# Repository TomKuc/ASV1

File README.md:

# Ankle Sensor V1 — A1 warunki produkcyjne A01–A04

**CONDITIONAL READY dla3–5 prototypów JLCPCB.** Można rozpocząć wycenę/import i przegląd JLCPCB. Zwolnienie wykonania wymaga zamknięcia warunków A01–A04 z [raportu gotowości](docs/production_readiness_A1.md). Nie złożono zamówienia i nie wykonano testów sprzętowych. Nie ma jeszcze uruchomionego firmware.

Jedyna aktualna wersja: [manifest A1](reports/current_A1_manifest.json). PCB SHA256: `1d3bb700a2b686ef68589bf3295488d2144a1d51a857cec7651e45be175a6134`. Aktualna paczka: **Ankle_Sensor_V1_A1_PRODUCTION_REVIEW.zip**. Dawne ZIP A0/A1/AUDIT/FINAL i raporty bazowe są historią.

## Co otwierać

- [Projekt KiCad](hardware/Ankle_Sensor_V1.kicad_pro), [schemat](hardware/Ankle_Sensor_V1.kicad_sch), [poprowadzone PCB](hardware/Ankle_Sensor_V1.kicad_pcb). Obok musi pozostać [plik reguł](hardware/Ankle_Sensor_V1.kicad_dru); zawiera uzasadnioną regułę tylko dla pary USB.
- [PDF schematu](reports/Ankle_Sensor_V1_A1_schematic.pdf), [STEP do przeglądu](reports/Ankle_Sensor_V1_A1_mechanical_review.step), [render KiCad](reports/Ankle_Sensor_V1_A1_3d_review.png), [przewodnik dla początkujących](reports/guide/ankle_sensor_przewodnik.html).
- [BOM](manufacturing/review/assembly/BOM_REVIEW_NOT_RELEASED.csv), [CPL/Pick and Place](manufacturing/review/assembly/CPL_REVIEW_ROTATIONS_UNCONFIRMED.csv), [Gerber/Drill](manufacturing/review/Ankle_Sensor_V1_A1_GERBERS_DRILL_REVIEW.zip), [manifest eksportu](manufacturing/review/export_manifest.json).
- [Warunki zamówienia A/B/C](docs/release_checklist.md), [wybrany profil JLCPCB](hardware/manufacturing_profile_A1.json), [tabela stanów ładowania](docs/charge_startup_final_A1.md), [USB i obliczenia](docs/production_usb_A1.md), [PCBA i DFM](docs/production_pcba_dfm_A1.md).

## Stan projektu

69 footprintów,59 części montowanych na TOP,4 warstwy, obrys30×51.6mm, nominalnie1.0mm. Pamięć **W25Q01JVZEIQ128MiB** pozostaje; nie zmieniono architektury. INT1=P0.11, INT2=P0.12. Zachowano centra wszystkich ścieżek, via i części. W tym etapie zmieniono tylko C9 na 10 µF / CL10A106KP8NNNC / C19702 w tym samym 0603. Pełna geometria PCB jest identyczna z poprzednim etapem; USB pozostaje 0.17/0.13 mm.

Wybrany profil do potwierdzenia zamówienia to **JLC7628 4L/1.0mm, outer1oz/inner0.5oz, zielona maska/ENIG**. Model2D trunku daje około94Ω względem In1 i87Ω przy idealnym warunkowym odniesieniu pobliskiej3V0. Nie jest to kwalifikacja całego toru ani fizyczny test USB. Ogólny plik Gerber Job KiCad jest oddzielnym plikiem referencyjnym, wyłączonym z ZIP do uploadu.

Natywne KiCad10.0.7: **ERC0 błędów/2 uzasadnione ostrzeżenia IMU; DRC0 naruszeń,0opens,0rozbieżności schemat–PCB, brak ignorowanych klas**. [Wyniki i hashe wejść](reports/validation_status.json). Sprawdzono współrzędne59 CPL,164vias,4sloty PTH i2NPTH względem PCB. Nie zatwierdzono jeszcze podglądu rotacji/MPN/panelu w JLCPCB.

R24 jest pull-up: HIGH/HiZ blokuje ładowanie; LOW zwalnia je tylko za zgodą sprzętowego okna. Hang LOW i System OFF wymagają jawnej obsługi firmware. **Bez działającego firmware bateria nie ładuje się**, ale USB może zasilać SYS i umożliwić programowanie przez SWD. Pakiet/wiązka/NTC są oddzielnym zespołem i wymagają kwalifikacji przed prawdziwym ładowaniem.

A01–A04: **EXTERNAL CONFIRMATION**. C11/Ceff i dokładne landy U3/J1/Y1 do akceptacji; aktualny stack, procurement/rotacje oraz CAM/DFM do JLC. [Gotowe pytania do producentów](docs/JLCPCB_A1_confirmation_request.md), [59 części i 3 pozycje zewnętrzne](reports/production_component_status_A1.csv). Testy Flash/IMU/BLE/USB/termiki wykonuje się po otrzymaniu prototypów. Zachowano [20 prób Flash, wszystkie NOT_RUN](docs/flash_firmware_test_plan_A1.md).

STEP jest niekompletny: brak USB-C, ogólny Raytac, gabaryt Flash i ograniczenie wysokości IMU. Bateria/obudowa nie są w modelu. [Ograniczenia mechaniczne](docs/mechanical_model_review.md).

## Historia i GitHub

`b5487d09…` to A1 sprzed audytu; `38545441…` po audycie; `cdcbd234…` poprzednia korekta USB; `1d3bb700…` obecna korekta nominału C9. [Pochodzenie i zachowane paczki](reports/production_provenance_A1.json).

Bazowy lokalny commit: b17f145. Nie potwierdzono ce616878 ani aktualnej rewizji na GitHubie; nie wykonano push. Nowy commit i bundle opisuje `reports/production_commit_delivery_A1.json`, dostarczany po utworzeniu commita. [Import i weryfikacja serwera](docs/github_delivery_production_A1.md).

Natywne pliki `hardware/` są źródłem projektu. `build_pcb.py --replace` usuwa routing, a `build_design.py` nadpisuje schematy — nie uruchamiać ich na tej A1 bez zabezpieczonej kopii. `sh scripts/kicad_cli.sh` izoluje cache KiCad w `.work`. Przegląd, obliczenia i eksporty nie zastępują testów prototypu ani akceptacji zamówienia.

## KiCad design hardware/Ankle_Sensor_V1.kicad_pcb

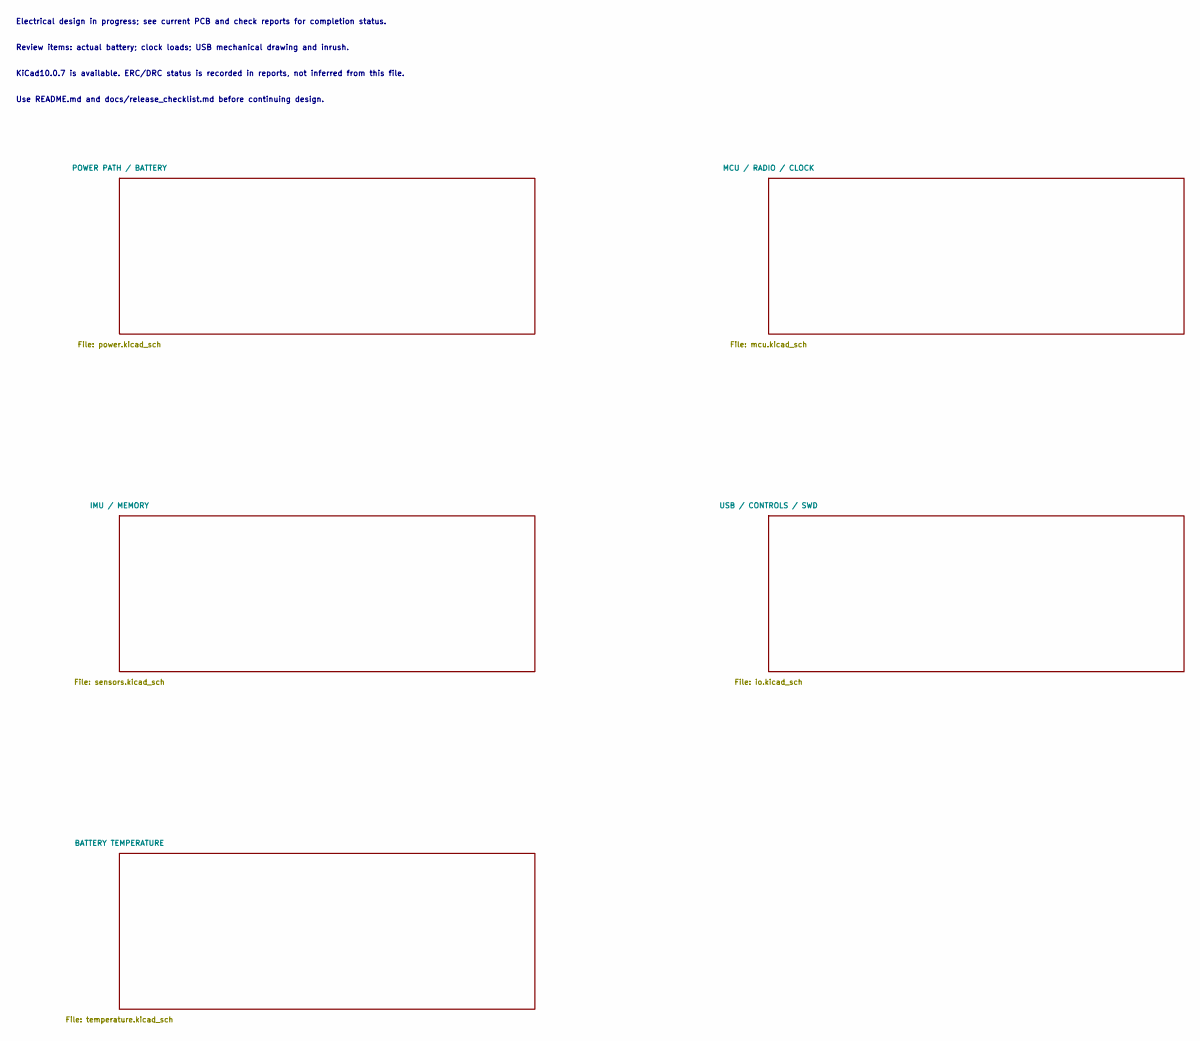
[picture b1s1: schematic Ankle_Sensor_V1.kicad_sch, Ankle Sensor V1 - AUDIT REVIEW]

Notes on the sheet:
Electrical design in progress; see current PCB and check reports for completion status.
Review items: actual battery; clock loads; USB mechanical drawing and inrush.
KiCad10.0.7 is available. ERC/DRC status is recorded in reports, not inferred from this file.
Use README.md and docs/release_checklist.md before continuing design.

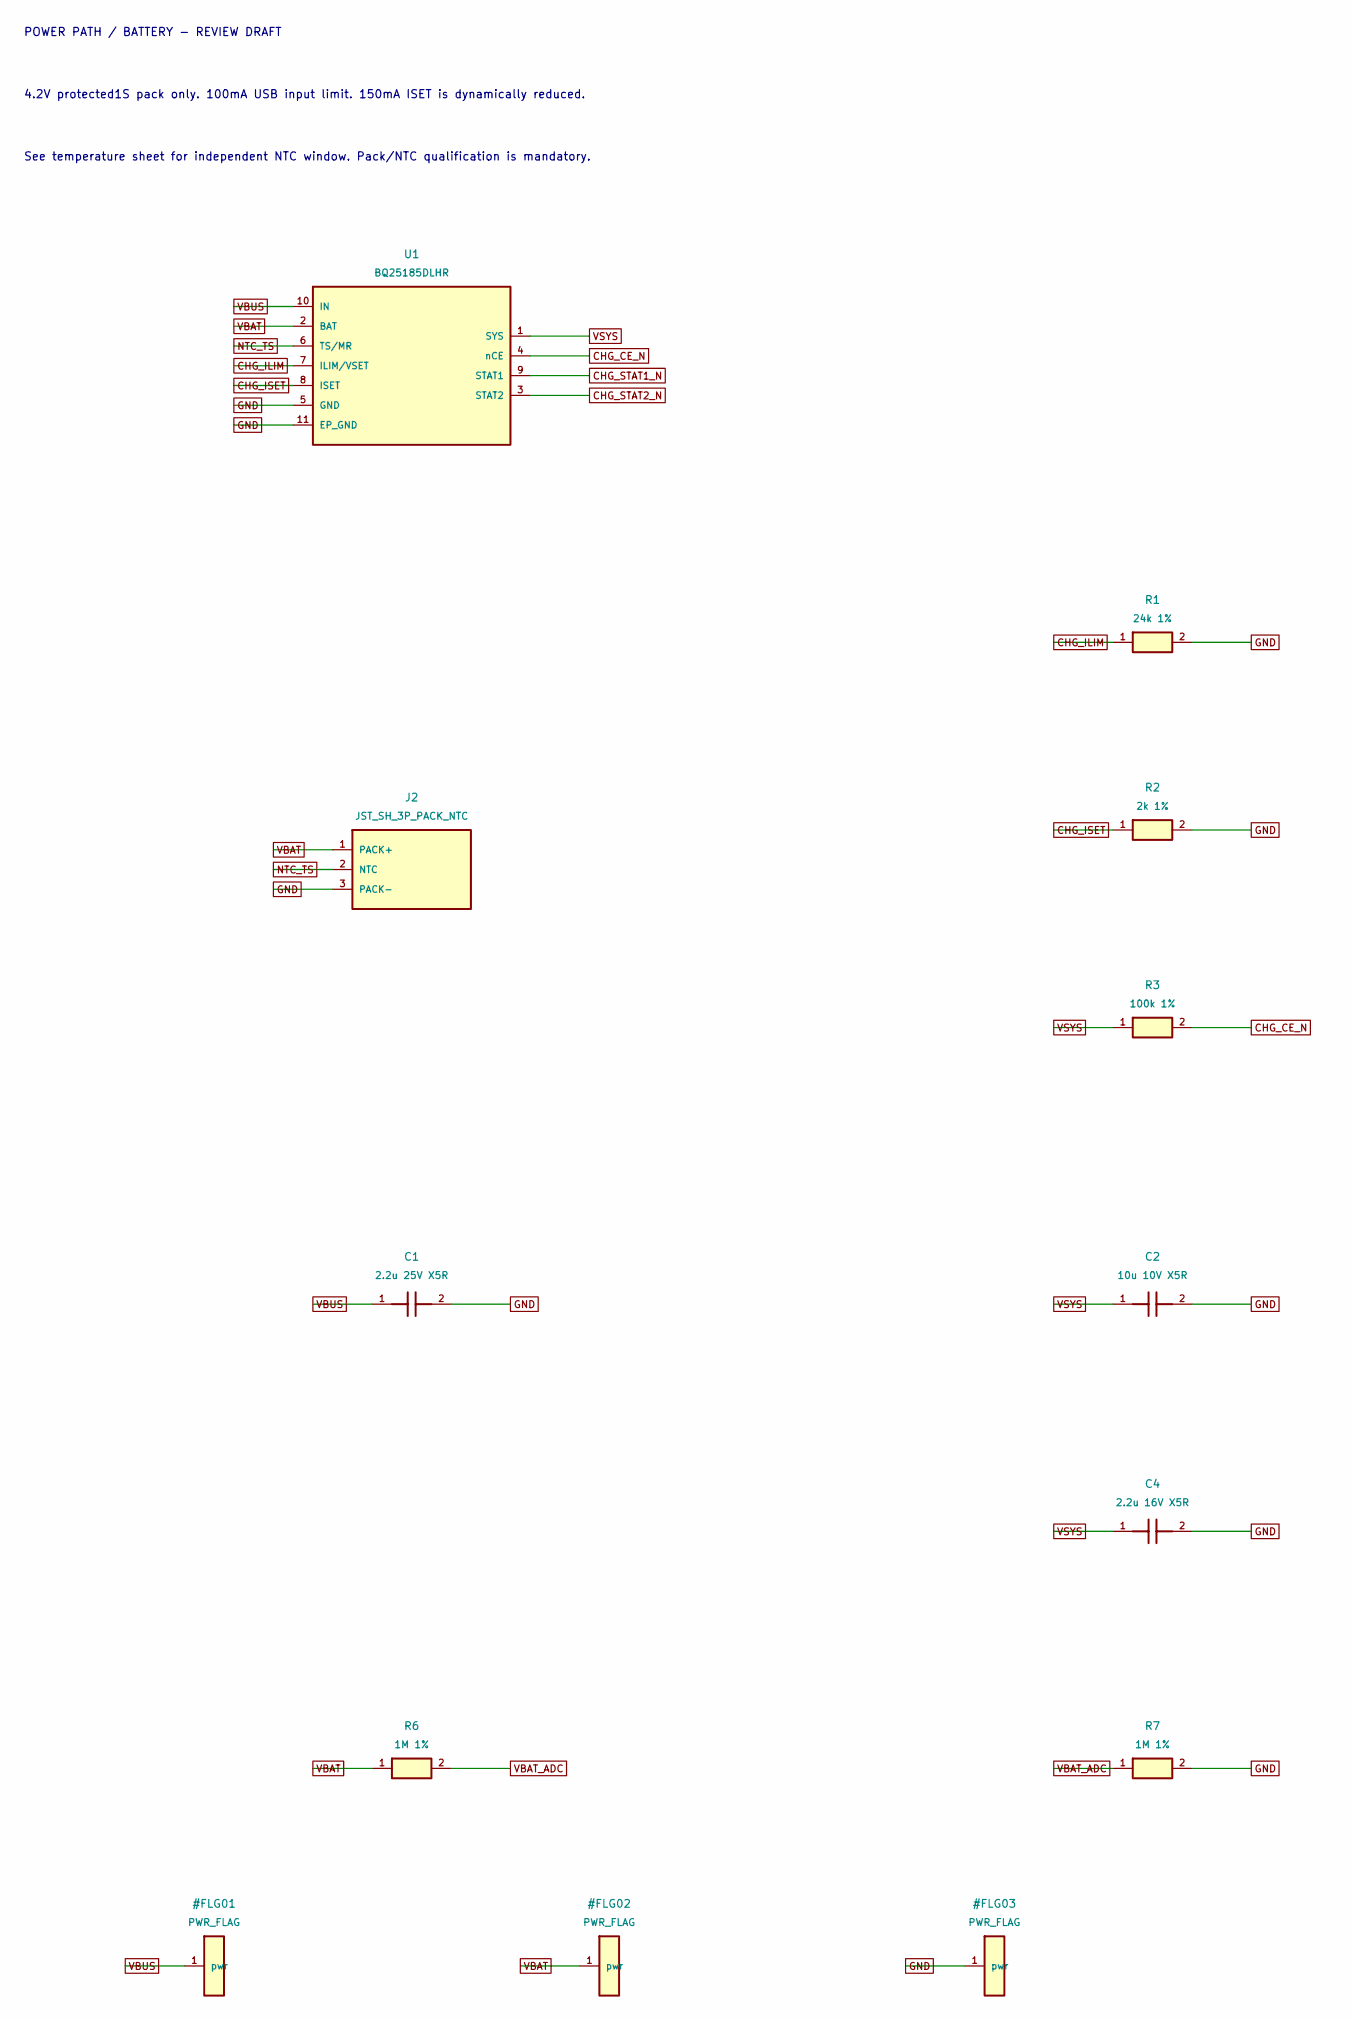
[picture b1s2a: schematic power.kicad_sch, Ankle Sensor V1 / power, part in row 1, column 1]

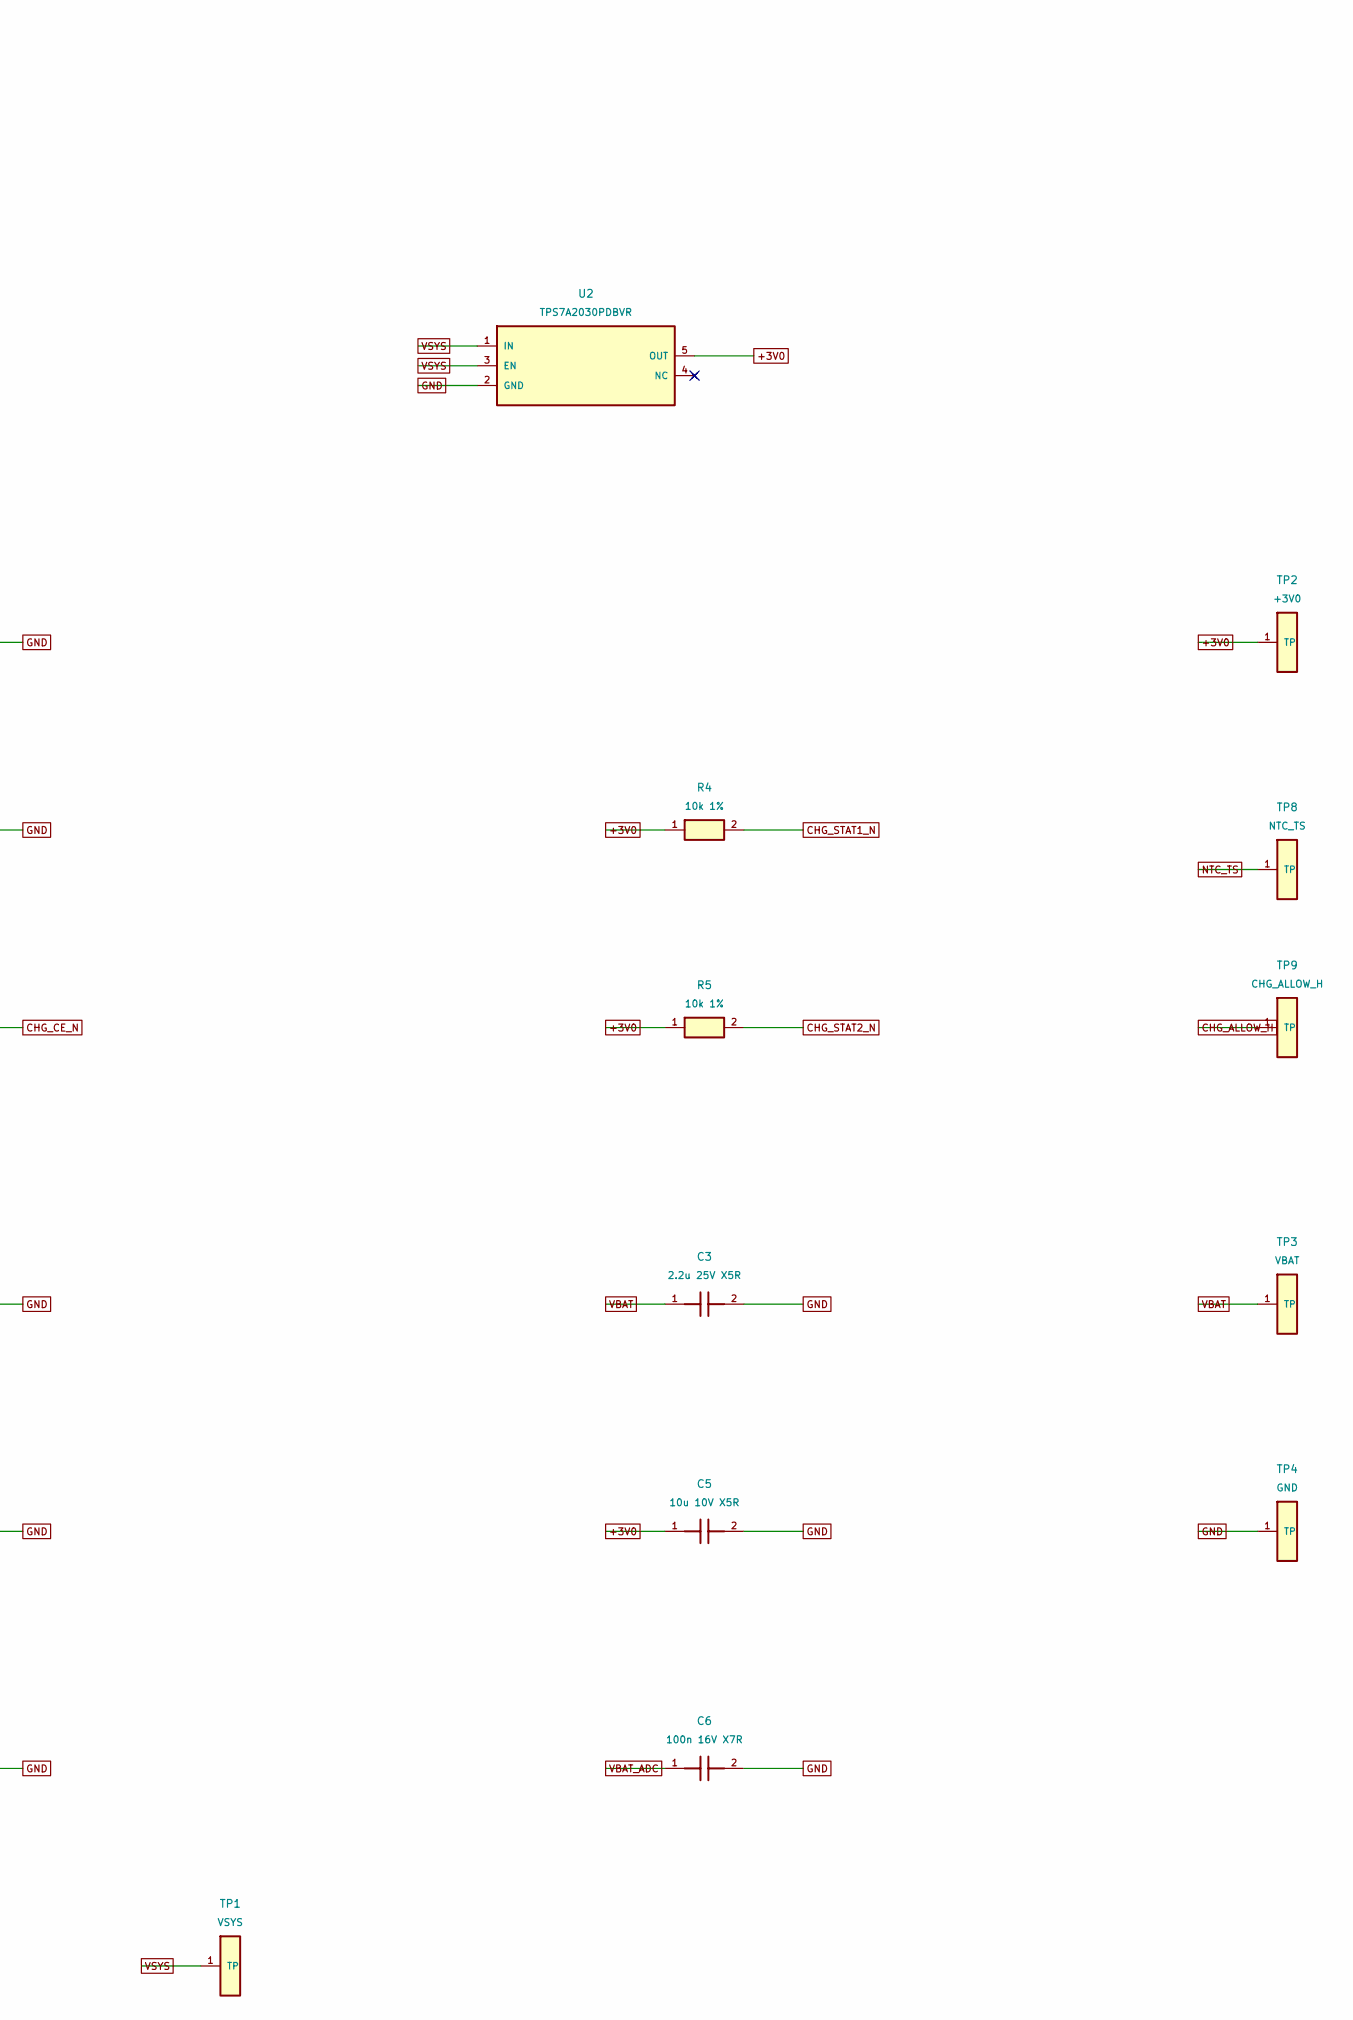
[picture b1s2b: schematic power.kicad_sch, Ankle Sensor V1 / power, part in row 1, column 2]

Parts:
C1, C3: 2.2u 25V X5R; C_0603_1608Metric; MPN CL10A225KA8NNNC; JLCPCB C57895
C2, C5: 10u 10V X5R; C_0603_1608Metric; MPN CL10A106KP8NNNC; JLCPCB C19702
C4: 2.2u 16V X5R; C_0603_1608Metric; MPN CL10A225KO8NNNC; JLCPCB C23630
C6: 100n 16V X7R; C_0402_1005Metric; MPN CL05B104KO5NNNC; JLCPCB C1525
J2: JST_SH_3P_PACK_NTC; JST_SH_SM03B-SRSS-TB_1x03-1MP_P1.00mm_Horizontal; MPN SM03B-SRSS-TB(LF)(SN); JLCPCB C160403
R1: 24k 1%; R_0402_1005Metric; MPN 0402WGF2402TCE; JLCPCB C25769
R2: 2k 1%; R_0402_1005Metric; MPN RC0402FR-072KL; JLCPCB C60488
R3: 100k 1%; R_0402_1005Metric; MPN 0402WGF1003TCE; JLCPCB C25741
R4, R5: 10k 1%; R_0402_1005Metric; MPN 0402WGF1002TCE; JLCPCB C25744
R6, R7: 1M 1%; R_0402_1005Metric; MPN 0402WGF1004TCE; JLCPCB C26083
TP1: VSYS; TestPoint_Pad_D1.0mm
TP2: +3V0; TestPoint_Pad_D1.0mm
TP3: VBAT; TestPoint_Pad_D1.0mm
TP4: GND; TestPoint_Pad_D1.0mm
TP8: NTC_TS; TestPoint_Pad_D1.0mm
TP9: CHG_ALLOW_H; TestPoint_Pad_D1.0mm
U1: BQ25185DLHR; BQ25185DLHR_DLH0010A_TILandPattern; MPN BQ25185DLHR; JLCPCB C19725033
U2: TPS7A2030PDBVR; SOT-23-5; MPN TPS7A2030PDBVR; JLCPCB C963429

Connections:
+3V0: C5.1, R4.1, R5.1, TP2.1, U2.5 (OUT); also elsewhere on the board
CHG_ALLOW_H: TP9.1; also elsewhere on the board
CHG_CE_N: R3.2, U1.4 (nCE); also elsewhere on the board
CHG_ILIM: R1.1, U1.7 (ILIM/VSET)
CHG_ISET: R2.1, U1.8 (ISET)
CHG_STAT1_N: R4.2, U1.9 (STAT1); also elsewhere on the board
CHG_STAT2_N: R5.2, U1.3 (STAT2); also elsewhere on the board
GND: C1.2, C2.2, C3.2, C4.2, C5.2, C6.2, J2.3 (PACK-), R1.2, R2.2, R7.2, TP4.1, U1.5 (GND), U1.11 (EP_GND), U2.2 (GND); also elsewhere on the board
NTC_TS: J2.2 (NTC), TP8.1, U1.6 (TS/MR); also elsewhere on the board
VBAT: C3.1, J2.1 (PACK+), R6.1, TP3.1, U1.2 (BAT)
VBAT_ADC: C6.1, R6.2, R7.1; also elsewhere on the board
VBUS: C1.1, U1.10 (IN); also elsewhere on the board
VSYS: C2.1, C4.1, R3.1, TP1.1, U1.1 (SYS), U2.1 (IN), U2.3 (EN)

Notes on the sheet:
POWER PATH / BATTERY - REVIEW DRAFT
4.2V protected1S pack only. 100mA USB input limit. 150mA ISET is dynamically reduced.
See temperature sheet for independent NTC window. Pack/NTC qualification is mandatory.

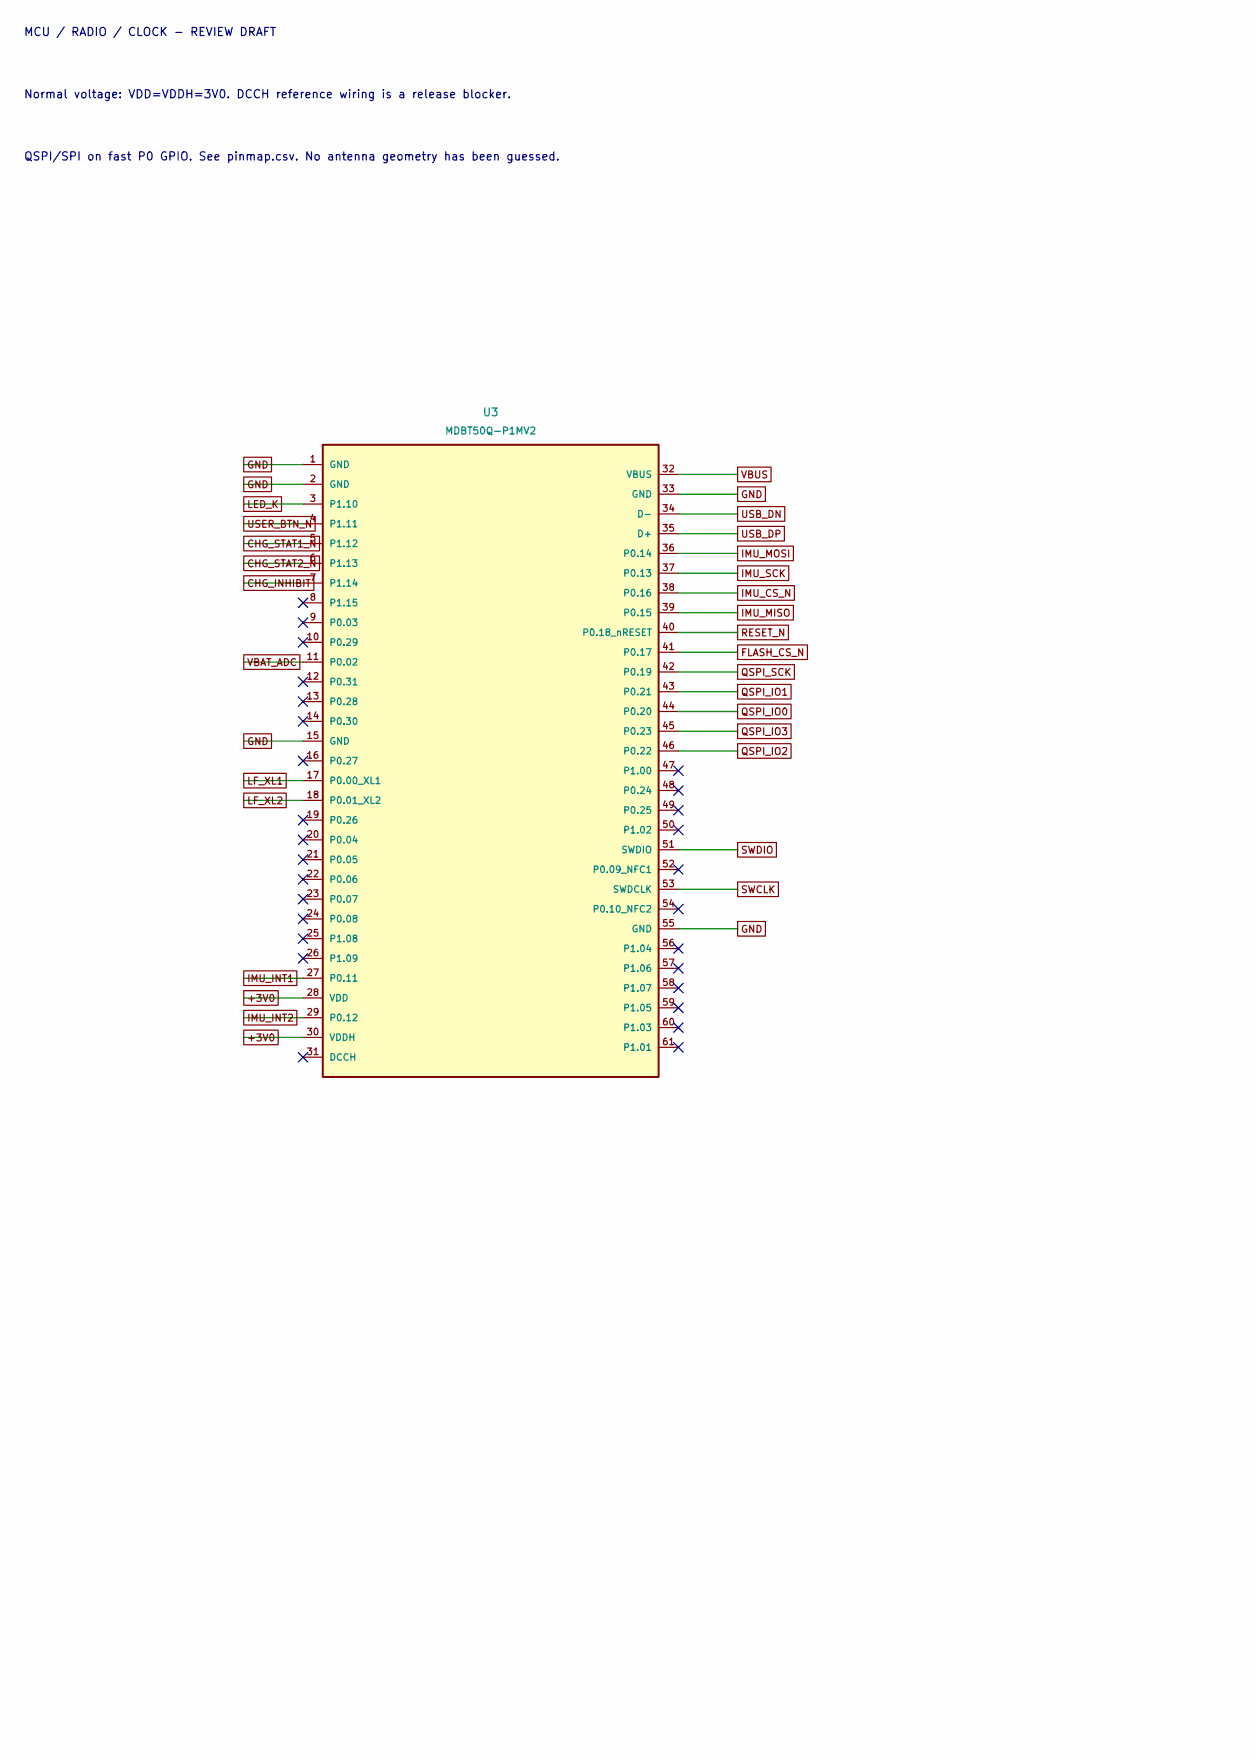
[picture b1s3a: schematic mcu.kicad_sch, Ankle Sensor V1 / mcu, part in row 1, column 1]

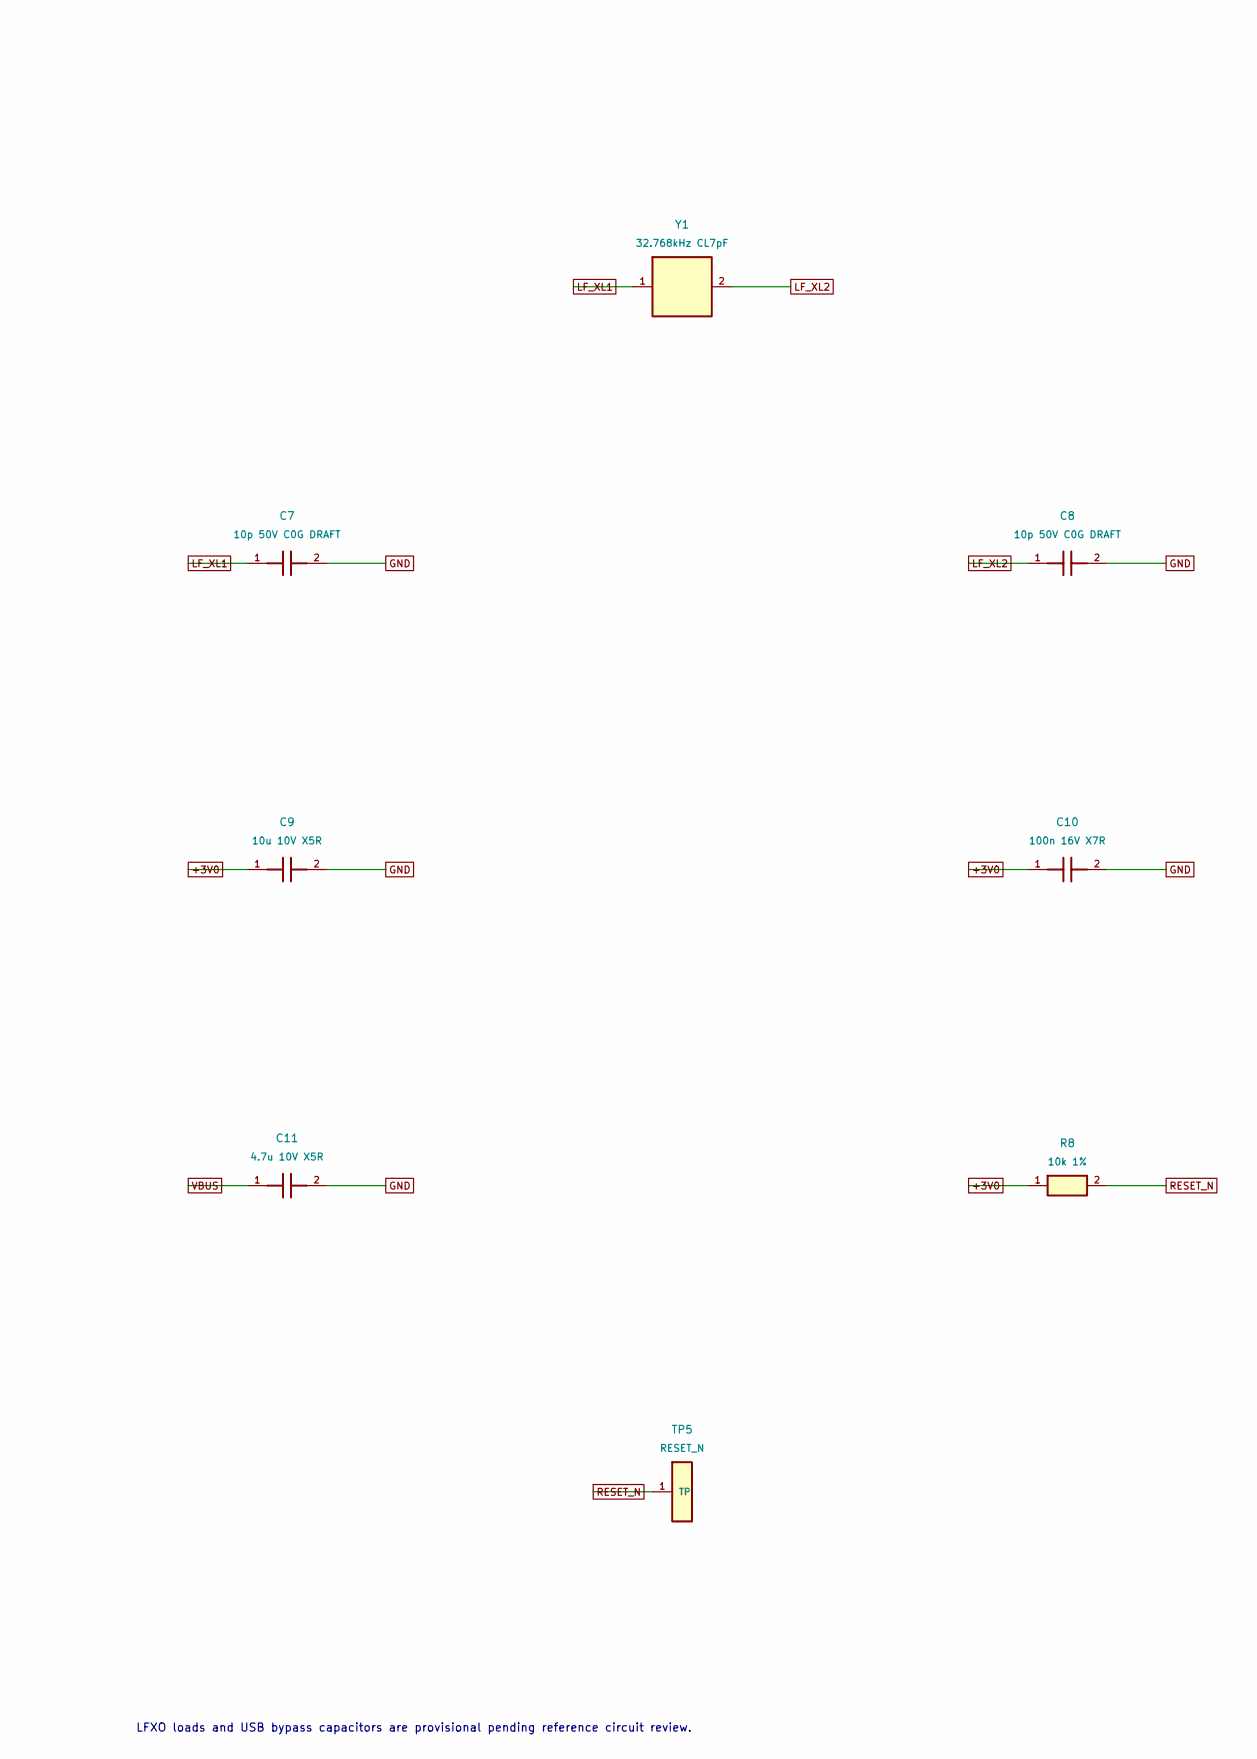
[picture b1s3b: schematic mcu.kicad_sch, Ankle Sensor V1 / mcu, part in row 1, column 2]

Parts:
C7, C8: 10p 50V C0G DRAFT; C_0402_1005Metric; MPN CL05C100JB5NNNC; JLCPCB C32949
C9: 10u 10V X5R; C_0603_1608Metric; MPN CL10A106KP8NNNC; JLCPCB C19702
C10: 100n 16V X7R; C_0402_1005Metric; MPN CL05B104KO5NNNC; JLCPCB C1525
C11: 4.7u 10V X5R; C_0603_1608Metric; MPN CL10A475KP8NNNC; JLCPCB C1705
R8: 10k 1%; R_0402_1005Metric; MPN 0402WGF1002TCE; JLCPCB C25744
TP5: RESET_N; TestPoint_Pad_D1.0mm
U3: MDBT50Q-P1MV2; Raytac_MDBT50Q; MPN MDBT50Q-P1MV2; JLCPCB C5119772
Y1: 32.768kHz CL7pF; Crystal_SMD_3215-2Pin_3.2x1.5mm; MPN ABS07-32.768KHZ-7-T; JLCPCB C276424

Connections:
+3V0: C9.1, C10.1, R8.1, U3.28 (VDD), U3.30 (VDDH); also elsewhere on the board
CHG_INHIBIT: U3.7 (P1.14); also elsewhere on the board
CHG_STAT1_N: U3.5 (P1.12); also elsewhere on the board
CHG_STAT2_N: U3.6 (P1.13); also elsewhere on the board
FLASH_CS_N: U3.41 (P0.17); also elsewhere on the board
GND: C7.2, C8.2, C9.2, C10.2, C11.2, U3.1 (GND), U3.2 (GND), U3.15 (GND), U3.33 (GND), U3.55 (GND); also elsewhere on the board
IMU_CS_N: U3.38 (P0.16); also elsewhere on the board
IMU_INT1: U3.27 (P0.11); also elsewhere on the board
IMU_INT2: U3.29 (P0.12); also elsewhere on the board
IMU_MISO: U3.39 (P0.15); also elsewhere on the board
IMU_MOSI: U3.36 (P0.14); also elsewhere on the board
IMU_SCK: U3.37 (P0.13); also elsewhere on the board
LED_K: U3.3 (P1.10); also elsewhere on the board
LF_XL1: C7.1, U3.17 (P0.00_XL1), Y1.1
LF_XL2: C8.1, U3.18 (P0.01_XL2), Y1.2
QSPI_IO0: U3.44 (P0.20); also elsewhere on the board
QSPI_IO1: U3.43 (P0.21); also elsewhere on the board
QSPI_IO2: U3.46 (P0.22); also elsewhere on the board
QSPI_IO3: U3.45 (P0.23); also elsewhere on the board
QSPI_SCK: U3.42 (P0.19); also elsewhere on the board
RESET_N: R8.2, TP5.1, U3.40 (P0.18_nRESET); also elsewhere on the board
SWCLK: U3.53 (SWDCLK); also elsewhere on the board
SWDIO: U3.51 (SWDIO); also elsewhere on the board
USB_DN: U3.34 (D-); also elsewhere on the board
USB_DP: U3.35 (D+); also elsewhere on the board
USER_BTN_N: U3.4 (P1.11); also elsewhere on the board
VBAT_ADC: U3.11 (P0.02); also elsewhere on the board
VBUS: C11.1, U3.32 (VBUS); also elsewhere on the board

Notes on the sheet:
MCU / RADIO / CLOCK - REVIEW DRAFT
Normal voltage: VDD=VDDH=3V0. DCCH reference wiring is a release blocker.
QSPI/SPI on fast P0 GPIO. See pinmap.csv. No antenna geometry has been guessed.
LFXO loads and USB bypass capacitors are provisional pending reference circuit review.

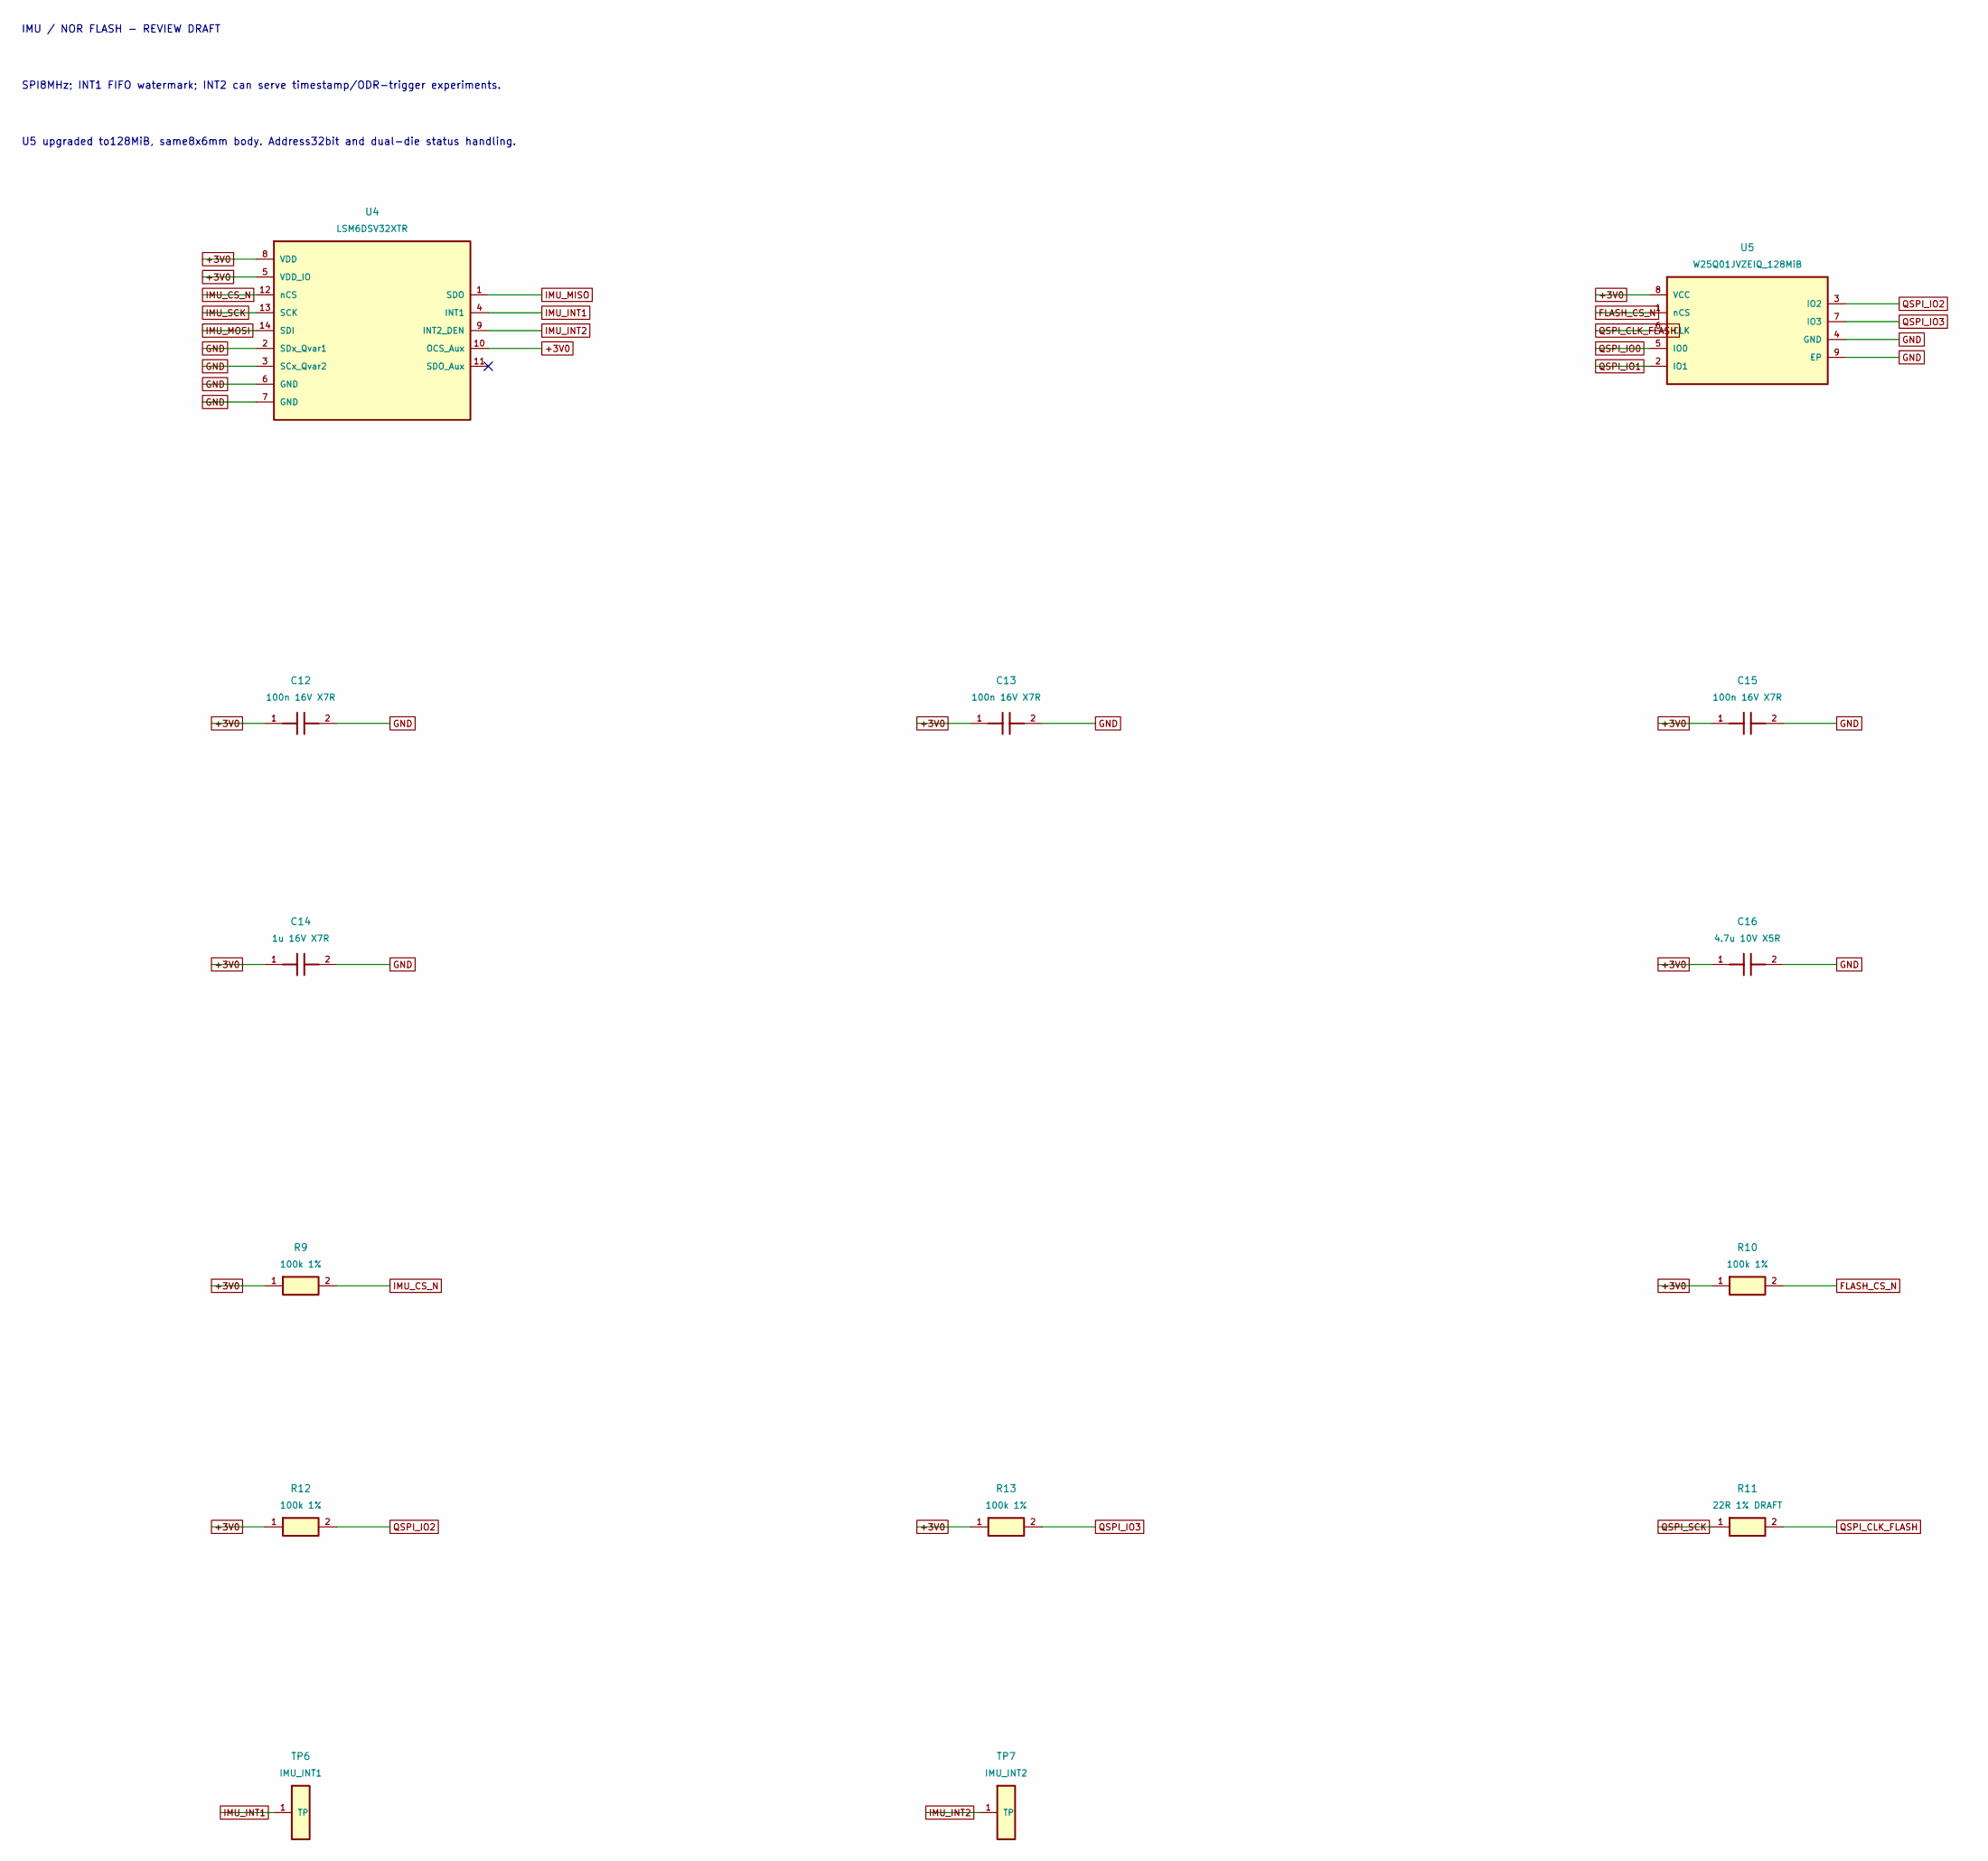
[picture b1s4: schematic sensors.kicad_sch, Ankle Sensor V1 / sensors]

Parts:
C12, C13, C15: 100n 16V X7R; C_0402_1005Metric; MPN CL05B104KO5NNNC; JLCPCB C1525
C14: 1u 16V X7R; C_0603_1608Metric; MPN CC0603KRX7R7BB105; JLCPCB C106248
C16: 4.7u 10V X5R; C_0603_1608Metric; MPN CL10A475KP8NNNC; JLCPCB C1705
R9, R10, R12, R13: 100k 1%; R_0402_1005Metric; MPN 0402WGF1003TCE; JLCPCB C25741
R11: 22R 1% DRAFT; R_0402_1005Metric; MPN 0402WGF220JTCE; JLCPCB C25092
TP6: IMU_INT1; TestPoint_Pad_D1.0mm
TP7: IMU_INT2; TestPoint_Pad_D1.0mm
U4: LSM6DSV32XTR; ST_LSM6DSV32X_LGA14_3x2.5mm_P0.5mm; MPN LSM6DSV32XTR; JLCPCB C22461202
U5: W25Q01JVZEIQ_128MiB; WSON-8-1EP_8x6mm_P1.27mm_EP3.4x4.3mm; MPN W25Q01JVZEIQ; JLCPCB C5137036

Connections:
+3V0: C12.1, C13.1, C14.1, C15.1, C16.1, R9.1, R10.1, R12.1, R13.1, U4.5 (VDD_IO), U4.8 (VDD), U4.10 (OCS_Aux), U5.8 (VCC); also elsewhere on the board
FLASH_CS_N: R10.2, U5.1 (nCS); also elsewhere on the board
GND: C12.2, C13.2, C14.2, C15.2, C16.2, U4.2 (SDx_Qvar1), U4.3 (SCx_Qvar2), U4.6 (GND), U4.7 (GND), U5.4 (GND), U5.9 (EP); also elsewhere on the board
IMU_CS_N: R9.2, U4.12 (nCS); also elsewhere on the board
IMU_INT1: TP6.1, U4.4 (INT1); also elsewhere on the board
IMU_INT2: TP7.1, U4.9 (INT2_DEN); also elsewhere on the board
IMU_MISO: U4.1 (SDO); also elsewhere on the board
IMU_MOSI: U4.14 (SDI); also elsewhere on the board
IMU_SCK: U4.13 (SCK); also elsewhere on the board
QSPI_CLK_FLASH: R11.2, U5.6 (CLK)
QSPI_IO0: U5.5 (IO0); also elsewhere on the board
QSPI_IO1: U5.2 (IO1); also elsewhere on the board
QSPI_IO2: R12.2, U5.3 (IO2); also elsewhere on the board
QSPI_IO3: R13.2, U5.7 (IO3); also elsewhere on the board
QSPI_SCK: R11.1; also elsewhere on the board

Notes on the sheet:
IMU / NOR FLASH - REVIEW DRAFT
SPI8MHz; INT1 FIFO watermark; INT2 can serve timestamp/ODR-trigger experiments.
U5 upgraded to128MiB, same8x6mm body. Address32bit and dual-die status handling.
